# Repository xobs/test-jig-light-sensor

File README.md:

# Light Sensor for Test Jig

This PCB defines a light sensor.  It can be used to determine whether an LED functions or not.  It was originally designed for use with the Chibitronics Love-to-Code project, and was adapted for the Fomu project.

It should be as thin as possible.  It was fabbed out on a 0.1mm flat-flex design.  It can be designed as either 1- or 2-layers, as necessary.

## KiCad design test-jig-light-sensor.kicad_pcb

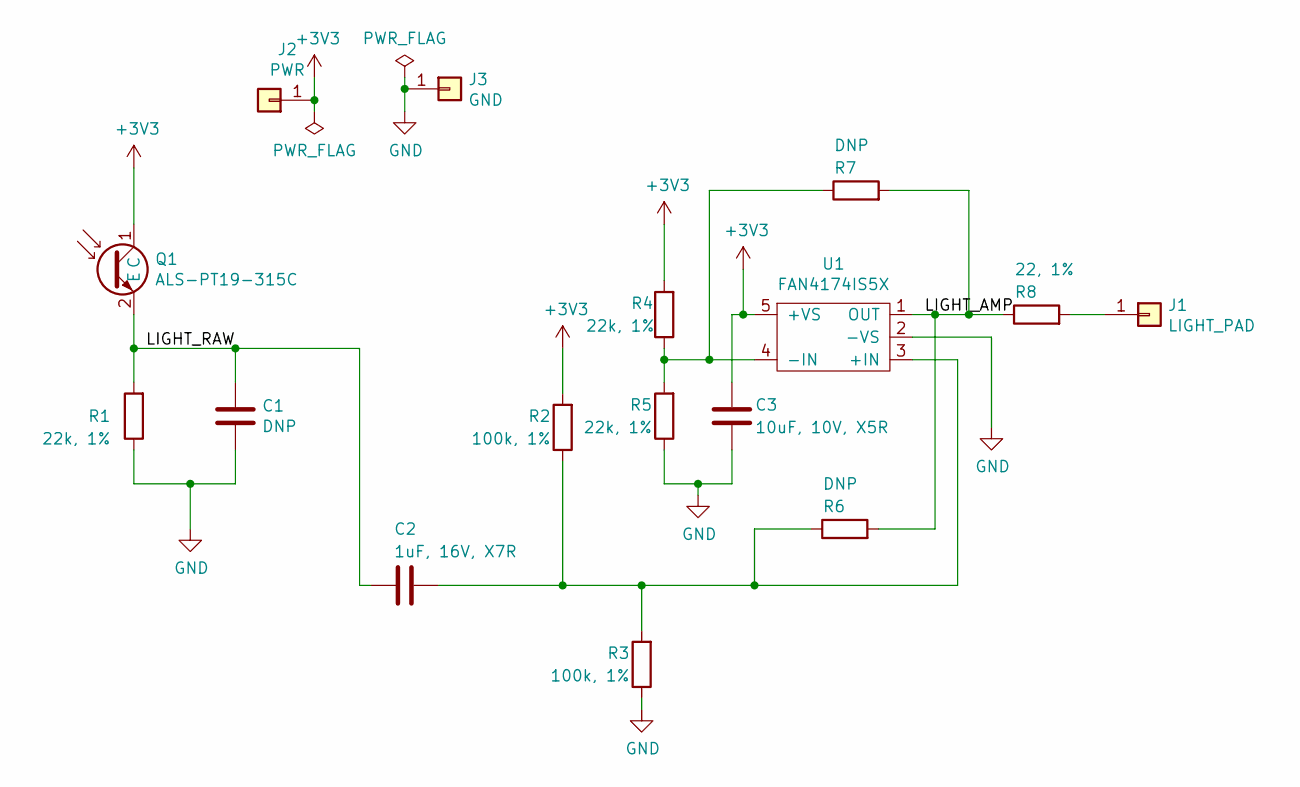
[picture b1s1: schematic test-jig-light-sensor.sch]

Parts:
C1: DNP; C_0603
C2: 1uF, 16V, X7R; C_0603
C3: 10uF, 10V, X5R; C_0603
J1: LIGHT_PAD; Pin_Header_Straight_1x01_Pitch2.54mm
J2: PWR; Pin_Header_Straight_1x01_Pitch2.54mm
J3: GND; Pin_Header_Straight_1x01_Pitch2.54mm
Q1: ALS-PT19-315C; MPN ALS-PT19-315C/L177/TR8
R1, R4, R5: 22k, 1%; R_0603
R2, R3: 100k, 1%; R_0603
R6, R7: DNP; R_0603
R8: 22, 1%; R_0603
U1: FAN4174IS5X; MPN FAN4174IS5X

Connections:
+3V3: C3.2, J2.1, Q1.1 (C), R2.2, R4.2, U1.5 (+VS)
/LIGHT_AMP: R6.2, R7.2, R8.1, U1.1 (OUT)
/LIGHT_RAW: C1.1, C2.2, Q1.2 (E), R1.2
GND: C1.2, C3.1, J3.1, R1.1, R3.1, R5.1, U1.2 (-VS)
unnamed: C2.1, R2.1, R3.2, R6.1, U1.3 (+IN)
unnamed: J1.1, R8.2
unnamed: R4.1, R5.2, R7.1, U1.4 (-IN)

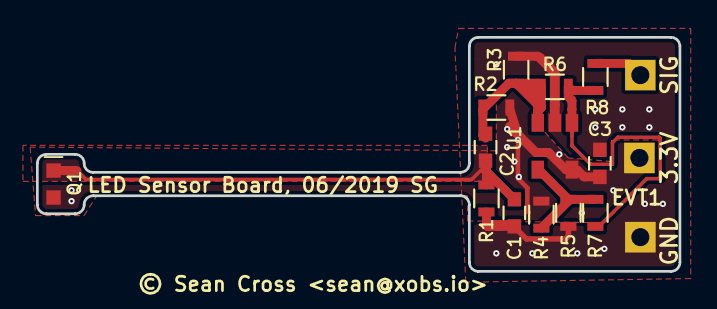
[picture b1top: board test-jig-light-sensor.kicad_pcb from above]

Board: 2 copper layers, 35.7 x 13.0 mm, 16 parts (0 on the bottom side), 7 nets.

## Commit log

2019-06-08 LICENSE: add TAPR license

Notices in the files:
test-jig-light-sensor.kicad_pcb:
© Sean Cross
